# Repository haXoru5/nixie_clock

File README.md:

# Nixie Clock

## Warning, Nixie Tubes require high voltages, use caution when handling

Retro style clock built using an Arduino and IN-14 Nixie tubes

## Intro
Nixie tubes are a type of cold cathode display. They were used as numerical displays as a precursor to seven-segment displays. This project uses old Soviet IN-14 tubes to make a clock. I used KiCad 5 to design the PCB, according to JLCPCB specifications. Although this is not an in depth build guide, feel free to use this as a reference for your own nixie projects.

### Key Components
#### Nixie Tubes
IN-14 tubes were used to display digits and IN-3 tubes were used as a decimal point and blinks to indicate seconds. Nixie tubes require very high voltages, so a custom power supply was required. Resistors were used to drop the voltage and current to the appropriate levels for each tube according to their datasheets.
#### Power Supply
The nixie tubes require high voltages, so a high voltage DC-DC converter was required to step up the voltage.
#### BCD Decoder IC
Due to the high voltage, specialty BCD decoders were required to drive the nixie tubes. Additionally, they are used to isolate the high voltages from the other components. They operate by connecting the cathode to ground to turn the appropriate digit on.
#### Real Time Clock
A battery powered Real Time Clock (RTC) is used to keep the time, even if the clock is powered off.
#### Arduino
The Arduino is the controlling module and the brain to the clock. It translates the clock information sent by the RTC and instructs the ICs to display the correct time.
## Schematic
The schematic was created as follows. Custom symbols were created for several components. The library containing all components is included in this repository [here](https://github.com/haXoru5/nixie_clock/tree/main/Nixie_KiCad). Several filter capacitors were used in this design. Voltage regulators were connected to the +12V and +5V outputs to ensure a constant voltage. (This is not required for the +170V output as the nixie tubes have a generous operating voltage range). Filter capacitors were also used to reduce ripple. Ripple may cause components to misbehave, and is best practice to mitigate it as much as possible. 0.33µF capacitors were used according to the voltage regulator datasheets. Generally, one 100nF capacitor is connected in parallel with each IC to reduce high frequency noise. another 10µF capacitor was used at the +5V output to reduce low frequency noise.

## PCB
After the schematic is created, I assigned footprints to the symbols and generated a netlist.
The netlist was used to create a ratsnest which could be used to create the PCB. I put all parts apart from the nixie tubes on the back side to ease mounting and presentation in the future. Mounting holes are also drilled to mount the PCB to its housing. Apart from the nixie tubes, all parts were standard sizes and had footprints already available in the KiCad footprint libraries. The custom footprints can be found in this repository [here](https://github.com/haXoru5/nixie_clock/tree/main/Nixie_KiCad). Note that due to the high voltages, trace clearance must be increased to 0.4mm. Track width can remain the same as current is not too high. Note that depending on the PCB manufacturer, additional default settings in Pcpnew may need to be adjusted.

## Housing
WIP
## Arduino Code
The Arduino code uses the DS3231 RTC to get hours, minutes, and seconds and converts it to a BDC to display on the Nixie tubes via the K155ID1 ICs.
### Board Specific Settings
Install the megaAVR package for the Arduino Nano Every.
Ensure register emulation is off.
### Libraries
The code requires two libraries, which can be installed using their ZIP package, or by searching in the Arduino IDE
- [RTClib](https://github.com/adafruit/RTClib)
- [Adafruit BusIO](https://github.com/adafruit/Adafruit_BusIO)
## Production
### Gerbers
Generating Gerber and drill files may depend on the PCB manufacturer. As I ordered my PCB from JLCPCB, I used [their specifications](https://support.jlcpcb.com/article/149-how-to-generate-gerber-and-drill-files-in-kicad).

### Parts
The parts I used were sourced from a variety of suppliers. For a comprehensive parts list, refer to [the BOM](https://github.com/haXoru5/nixie_clock/blob/main/BOM.csv).

**Ebay**

IN-14 Nixie Tube
IN-3 Nixie Tube
High Voltage Power Supply
K155ID1 BCD Decoder IC

**Aliexpress**

DS3231 RTC
DIP Sockets
Female PCB Headers

**DigiKey**

L7812CV 12V Voltage Regulator
NJM78M05FA 5V Voltage Regulator
1/4W THT Resistors
SMT Capacitors

**Amazon**

Arduino Nano Every
### Assembly
WIP

### Future Releases
#### V2.0
- Programmable alarm function

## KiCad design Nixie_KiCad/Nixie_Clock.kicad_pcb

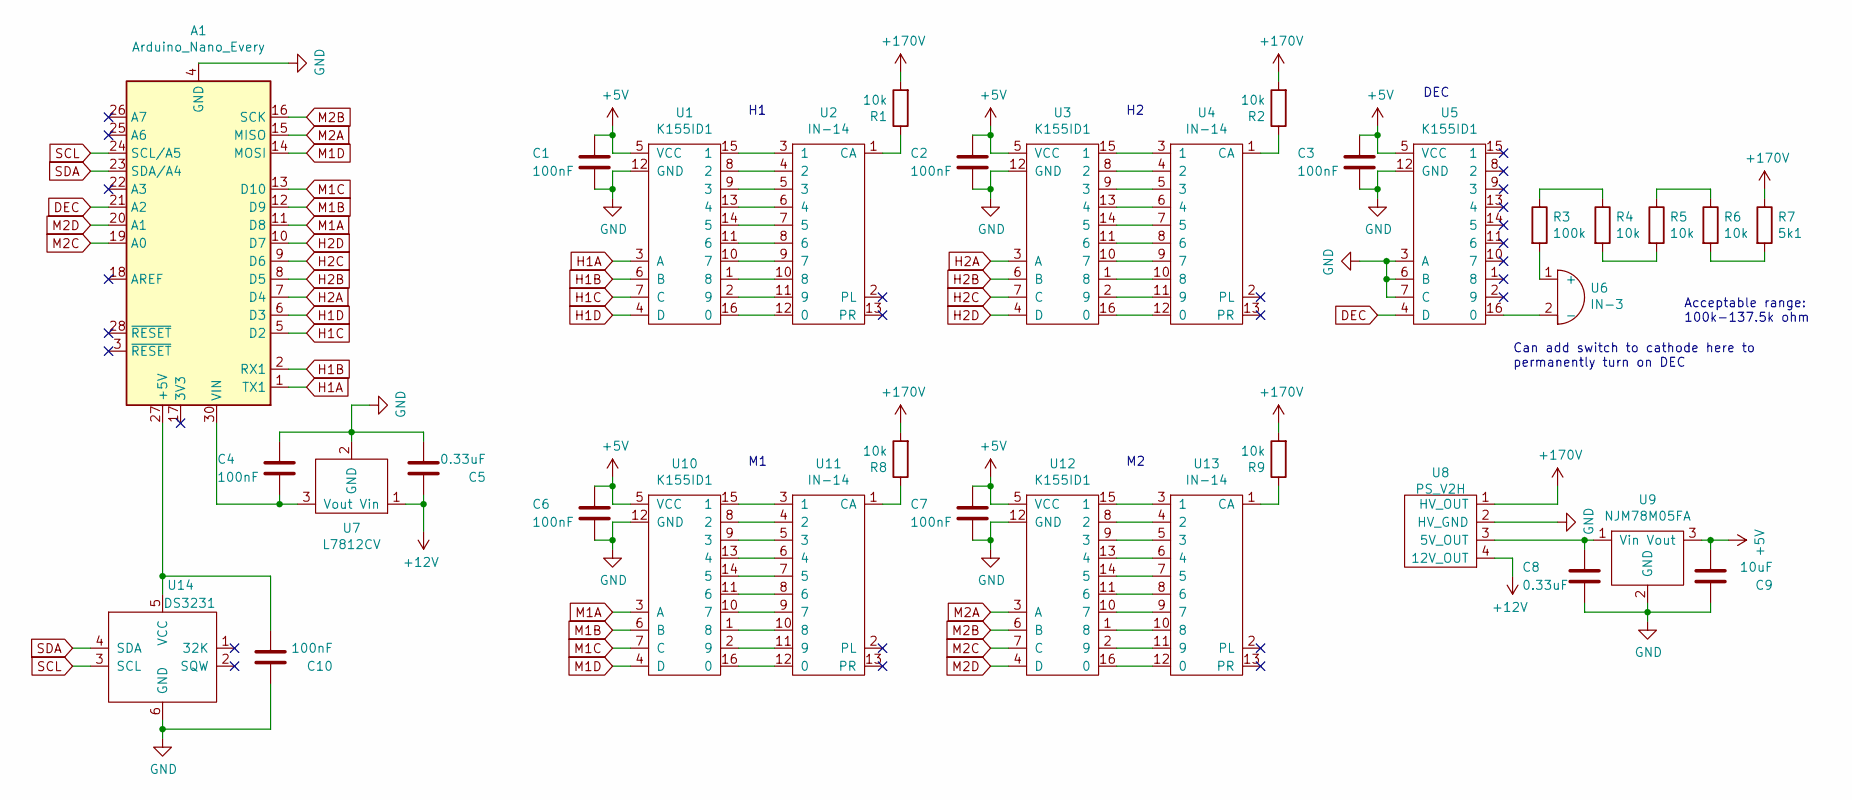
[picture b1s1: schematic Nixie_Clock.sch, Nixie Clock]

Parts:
A1: Arduino_Nano_Every; Arduino_Nano
C1, C2, C3, C4, C6, C7, C10: 100nF; C_0402_1005Metric_Pad0.74x0.62mm_HandSolder
C5, C8: 0.33uF; C_1206_3216Metric_Pad1.33x1.80mm_HandSolder
C9: 10uF; C_0805_2012Metric_Pad1.18x1.45mm_HandSolder
R1, R2, R4, R5, R6, R8, R9: 10k; R_Axial_DIN0207_L6.3mm_D2.5mm_P7.62mm_Horizontal
R3: 100k; R_Axial_DIN0207_L6.3mm_D2.5mm_P7.62mm_Horizontal
R7: 5k1; R_Axial_DIN0207_L6.3mm_D2.5mm_P7.62mm_Horizontal
U1, U3, U5, U10, U12: K155ID1
U2, U4, U11, U13: IN-14
U6: IN-3
U7: L7812CV; TO-220-3_Horizontal_TabDown
U8: PS_V2H
U9: NJM78M05FA‎; TO-220F-3_Horizontal_TabDown
U14: DS3231

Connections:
+5V: C1.2, C2.2, C3.2, C6.2, C7.2, C9.1, U1.5 (VCC), U3.5 (VCC), U5.5 (VCC), U9.3 (Vout), U10.5 (VCC), U12.5 (VCC)
+12V: C5.2, U7.1 (Vin), U8.4 (12V_OUT)
+170V: R1.2, R2.2, R7.1, R8.2, R9.2, U8.1 (HV_OUT)
DEC: A1.21 (A2), U5.4 (D)
GND: A1.4 (GND), A1.29 (GND), C1.1, C2.1, C3.1, C4.2, C5.1, C6.1, C7.1, C8.1, C9.2, C10.2, U1.12 (GND), U3.12 (GND), U5.3 (A), U5.6 (B), U5.7 (C), U5.12 (GND), U7.2 (GND), U8.2 (HV_GND), U9.2 (GND), U10.12 (GND), U12.12 (GND), U14.6 (GND)
H1A: A1.1 (TX1), U1.3 (A)
H1B: A1.2 (RX1), U1.6 (B)
H1C: A1.5 (D2), U1.7 (C)
H1D: A1.6 (D3), U1.4 (D)
H2A: A1.7 (D4), U3.3 (A)
H2B: A1.8 (D5), U3.6 (B)
H2C: A1.9 (D6), U3.7 (C)
H2D: A1.10 (D7), U3.4 (D)
M1A: A1.11 (D8), U10.3 (A)
M1B: A1.12 (D9), U10.6 (B)
M1C: A1.13 (D10), U10.7 (C)
M1D: A1.14 (MOSI), U10.4 (D)
M2A: A1.15 (MISO), U12.3 (A)
M2B: A1.16 (SCK), U12.6 (B)
M2C: A1.19 (A0), U12.7 (C)
M2D: A1.20 (A1), U12.4 (D)
unnamed: A1.27 (+5V), C10.1, U14.5 (VCC)
unnamed: A1.30 (VIN), C4.1, U7.3 (Vout)
unnamed: C8.2, U8.3 (5V_OUT), U9.1 (Vin)
unnamed: R1.1, U2.1 (CA)
unnamed: R2.1, U4.1 (CA)
unnamed: R3.1, R4.1
unnamed: R3.2, U6.1 (+)
unnamed: R4.2, R5.2
unnamed: R5.1, R6.1
unnamed: R6.2, R7.2
unnamed: R8.1, U11.1 (CA)
unnamed: R9.1, U13.1 (CA)
unnamed: U1.1 (8), U2.10 (8)
unnamed: U1.2 (9), U2.11 (9)
unnamed: U1.8 (2), U2.4 (2)
unnamed: U1.9 (3), U2.5 (3)
unnamed: U1.10 (7), U2.9 (7)
unnamed: U1.11 (6), U2.8 (6)
unnamed: U1.13 (4), U2.6 (4)
unnamed: U1.14 (5), U2.7 (5)
unnamed: U1.15 (1), U2.3 (1)
unnamed: U1.16 (0), U2.12 (0)
unnamed: U3.1 (8), U4.10 (8)
unnamed: U3.2 (9), U4.11 (9)
unnamed: U3.8 (2), U4.4 (2)
unnamed: U3.9 (3), U4.5 (3)
unnamed: U3.10 (7), U4.9 (7)
unnamed: U3.11 (6), U4.8 (6)
unnamed: U3.13 (4), U4.6 (4)
unnamed: U3.14 (5), U4.7 (5)
unnamed: U3.15 (1), U4.3 (1)
unnamed: U3.16 (0), U4.12 (0)
unnamed: U5.16 (0), U6.2 (-)
unnamed: U10.1 (8), U11.10 (8)
unnamed: U10.2 (9), U11.11 (9)
unnamed: U10.8 (2), U11.4 (2)
unnamed: U10.9 (3), U11.5 (3)
unnamed: U10.10 (7), U11.9 (7)
unnamed: U10.11 (6), U11.8 (6)
unnamed: U10.13 (4), U11.6 (4)
unnamed: U10.14 (5), U11.7 (5)
unnamed: U10.15 (1), U11.3 (1)
unnamed: U10.16 (0), U11.12 (0)
unnamed: U12.1 (8), U13.10 (8)
unnamed: U12.2 (9), U13.11 (9)
unnamed: U12.8 (2), U13.4 (2)
unnamed: U12.9 (3), U13.5 (3)
unnamed: U12.10 (7), U13.9 (7)
unnamed: U12.11 (6), U13.8 (6)
unnamed: U12.13 (4), U13.6 (4)
unnamed: U12.14 (5), U13.7 (5)
unnamed: U12.15 (1), U13.3 (1)
unnamed: U12.16 (0), U13.12 (0)
SCL: A1.24 (SCL/A5), U14.3 (SCL)
SDA: A1.23 (SDA/A4), U14.4 (SDA)

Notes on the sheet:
DEC
Acceptable range: 100k-137.5k ohm
Can add switch to cathode here to permanently turn on DEC

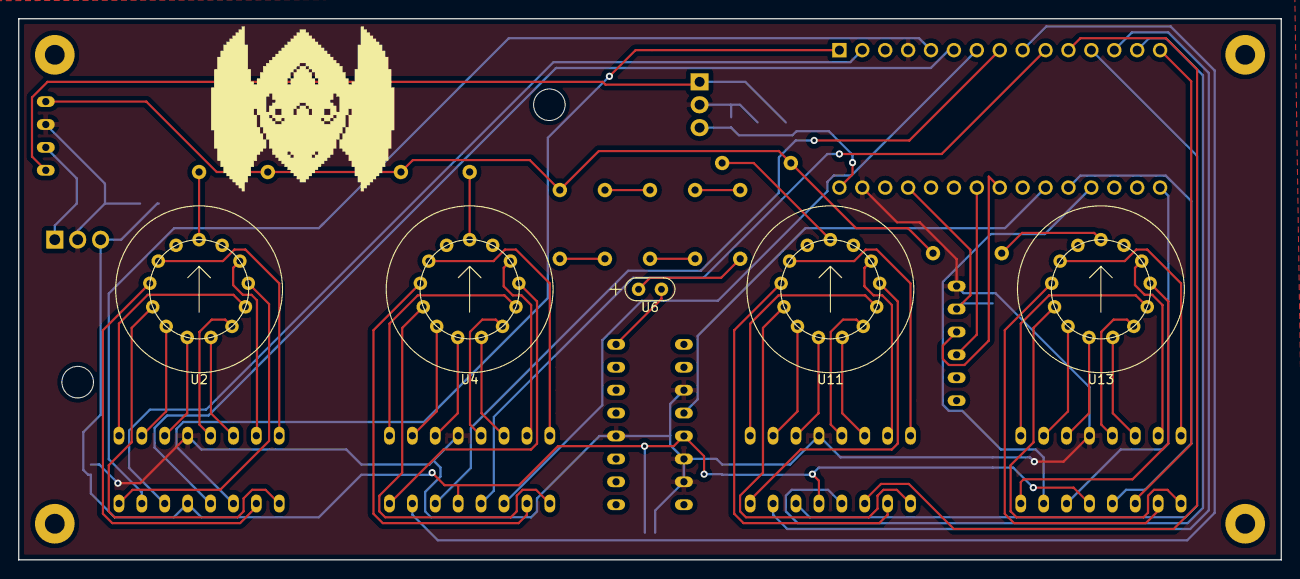
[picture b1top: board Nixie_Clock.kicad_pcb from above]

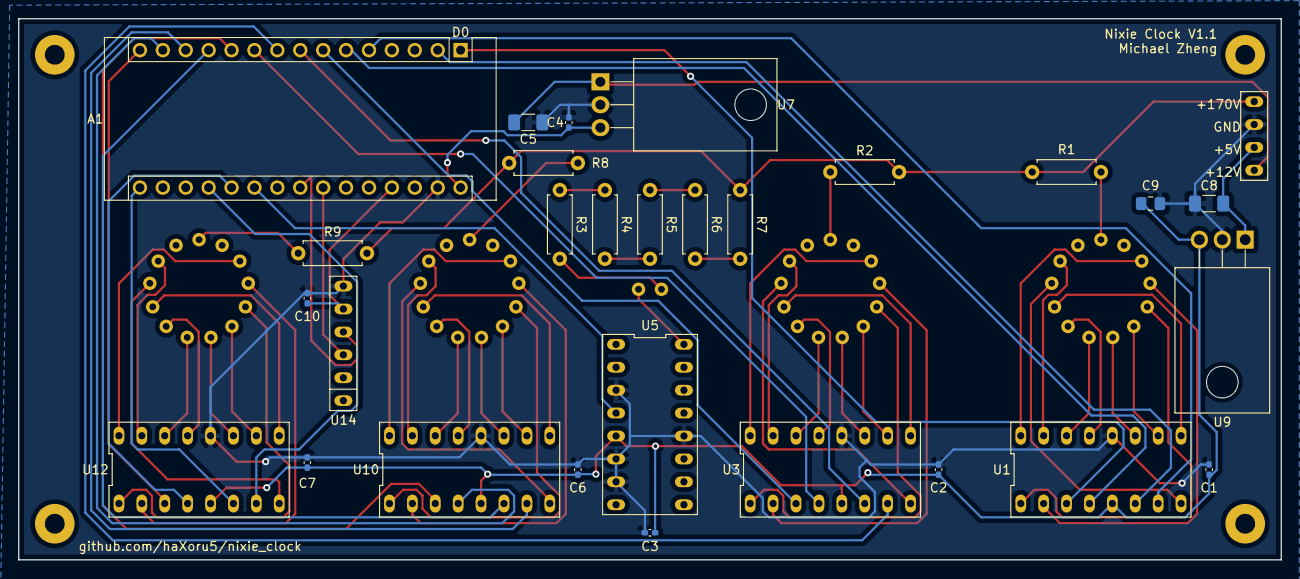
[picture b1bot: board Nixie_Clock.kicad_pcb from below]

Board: 2 copper layers, 140.0 x 60.0 mm, 34 parts (29 on the bottom side), 76 nets.

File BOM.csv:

Reference, Quantity, Value, Footprint, Datasheet
A1 ,1,Arduino_Nano_Every,Module:Arduino_Nano,https://content.arduino.cc/assets/NANOEveryV3.0_sch.pdf
C1 C2 C3 C4 C6 C7 C10 ,7,100nF,Capacitor_SMD:C_0402_1005Metric_Pad0.74x0.62mm_HandSolder,~
C5 C8 ,2,0.33uF,Capacitor_SMD:C_1206_3216Metric_Pad1.33x1.80mm_HandSolder,~
C9 ,1,10uF,Capacitor_SMD:C_0805_2012Metric_Pad1.18x1.45mm_HandSolder,~
R1 R2 R4 R5 R6 R8 R9 ,7,10k,Resistor_THT:R_Axial_DIN0207_L6.3mm_D2.5mm_P7.62mm_Horizontal,~
R3 ,1,100k,Resistor_THT:R_Axial_DIN0207_L6.3mm_D2.5mm_P7.62mm_Horizontal,~
R7 ,1,5k1,Resistor_THT:R_Axial_DIN0207_L6.3mm_D2.5mm_P7.62mm_Horizontal,~
U1 U3 U5 U10 U12 ,5,K155ID1,Nixie_Clock_Footprint:K155ID1,https://tubehobby.com/datasheets/k155id1.pdf
U2 U4 U11 U13 ,4,IN-14,Nixie_Clock_Footprint:IN-14,https://tubehobby.com/datasheets/in14.pdf
U14 ,1,DS3231,Nixie_Clock_Footprint:DS3231,https://datasheets.maximintegrated.com/en/ds/DS3231.pdf
U6 ,1,IN-3,Nixie_Clock_Footprint:IN-3,http://www.tube-tester.com/sites/nixie/dat_arch/IN-3.pdf
U7 ,1,L7812CV,Nixie_Clock_Footprint:SIP-3,https://www.st.com/content/ccc/resource/technical/document/d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
U8 ,1,PS_V2H,Nixie_Clock_Footprint:PS_V2H,https://github.com/haXoru5/nixie_clock/blob/main/Docs/PS_V2H.pdf
U9 ,1,NJM78M05FA?,Nixie_Clock_Footprint:SIP-3,https://www.nisshinbo-microdevices.co.jp/en/pdf/datasheet/NJ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

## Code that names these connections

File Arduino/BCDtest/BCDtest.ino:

#include "RTClib.h"

RTC_DS3231 rtc;

#define H1A 1
#define H1B 0
#define H1C 2
#define H1D 3
#define H2A 4
#define H2B 5
#define H2C 6
#define H2D 7
#define M1A 8
#define M1B 9
#define M1C 10
#define M1D 11
#define M2A 12
#define M2B 13
#define M2C A0
#define M2D A1
#define DECIMAL A2

char Apins[4] = {H1A, H2A, M1A, M2A};   //matrix to determine BCD output
char Bpins[4] = {H1B, H2B, M1B, M2B};
char Cpins[4] = {H1C, H2C, M1C, M2C};
char Dpins[4] = {H1D, H2D, M1D, M2D};
char Epins[1] = {DECIMAL};  //allows for future alarm to use same IC

#define H1 0
#define H2 1
#define M1 2
#define M2 3

void setup()
{
  Serial.begin(57600);

#ifndef ESP8266
  while (!Serial)
    ; // wait for serial port to connect. Needed for native USB
#endif

  if (!rtc.begin())
  {
    Serial.println("Couldn't find RTC");
    Serial.flush();
    while (1)
      delay(10);
  }
  if (rtc.lostPower())
  {
    Serial.println("RTC lost power, let's set the time!");
    rtc.adjust(DateTime(F(__DATE__), F(__TIME__)));   //sets RTC time if lost power
  }
    //rtc.adjust(DateTime(F(__DATE__), F(__TIME__)));   //uncomment to set time

  pinMode(H1A, OUTPUT);
  pinMode(H1B, OUTPUT);
  pinMode(H1C, OUTPUT);
  pinMode(H1D, OUTPUT);
  pinMode(H2A, OUTPUT);
  pinMode(H2B, OUTPUT);
  pinMode(H2C, OUTPUT);
  pinMode(H2D, OUTPUT);
  pinMode(M1A, OUTPUT);
  pinMode(M1B, OUTPUT);
  pinMode(M1C, OUTPUT);
  pinMode(M1D, OUTPUT);
  pinMode(M2A, OUTPUT);
  pinMode(M2B, OUTPUT);
  pinMode(M2C, OUTPUT);
  pinMode(M2D, OUTPUT);
  pinMode(DECIMAL, OUTPUT);

}

void loop()
{
  DateTime now = rtc.now();

  Serial.print(now.year(), DEC);
  Serial.print('/');
  Serial.print(now.month(), DEC);
  Serial.print('/');
  Serial.print(now.day(), DEC);
  Serial.println();
  Serial.print(now.hour(), DEC);
  Serial.print(':');
  Serial.print(now.minute(), DEC);
  Serial.print(':');
  Serial.print(now.second(), DEC);
  Serial.println();

  BCD(H1, now.hour() / 10);
  BCD(H2, now.hour() % 10);
  BCD(M1, now.minute() / 10);
  BCD(M2, now.minute() % 10);
  if (now.second() % 2 == 0)
  {
    digitalWrite(DECIMAL, HIGH);
    Serial.println("Dec = HIGH");
  }
  else
  {
    digitalWrite(DECIMAL, LOW);
    Serial.println("Dec = LOW");
  }
  delay(1000);
}

void BCD(int digit, int value)    //switch case determines BCD value to be sent, digit determines IC number BCD should be sent to
{
  Serial.print(digit);
  Serial.print("=");
  switch (value)
  {
    case 0:
        digitalWrite(Apins[digit], LOW);
        digitalWrite(Bpins[digit], LOW);
        digitalWrite(Cpins[digit], LOW);
        digitalWrite(Dpins[digit], LOW);
      Serial.println("0000");
      break;
    case 1:
        digitalWrite(Apins[digit], HIGH);
        digitalWrite(Bpins[digit], LOW);
        digitalWrite(Cpins[digit], LOW);
        digitalWrite(Dpins[digit], LOW);
      Serial.println("0001");
      break;
    case 2:
        digitalWrite(Apins[digit], LOW);
        digitalWrite(Bpins[digit], HIGH);
        digitalWrite(Cpins[digit], LOW);
        digitalWrite(Dpins[digit], LOW);
      Serial.println("0010");
      break;
    case 3:
        digitalWrite(Apins[digit], HIGH);
        digitalWrite(Bpins[digit], HIGH);
        digitalWrite(Cpins[digit], LOW);
        digitalWrite(Dpins[digit], LOW);
      Serial.println("0011");
      break;
    case 4:
        digitalWrite(Apins[digit], LOW);
        digitalWrite(Bpins[digit], LOW);
        digitalWrite(Cpins[digit], HIGH);
        digitalWrite(Dpins[digit], LOW);
      Serial.println("0100");
      break;
    case 5:
        digitalWrite(Apins[digit], HIGH);
        digitalWrite(Bpins[digit], LOW);
        digitalWrite(Cpins[digit], HIGH);
        digitalWrite(Dpins[digit], LOW);
      Serial.println("0101");
      break;
    case 6:
        digitalWrite(Apins[digit], LOW);
        digitalWrite(Bpins[digit], HIGH);
        digitalWrite(Cpins[digit], HIGH);
        digitalWrite(Dpins[digit], LOW);
      Serial.println("0110");
      break;
    case 7:
        digitalWrite(Apins[digit], HIGH);
        digitalWrite(Bpins[digit], HIGH);
        digitalWrite(Cpins[digit], HIGH);
        digitalWrite(Dpins[digit], LOW);
      Serial.println("0111");
      break;
    case 8:
        digitalWrite(Apins[digit], LOW);
        digitalWrite(Bpins[digit], LOW);
        digitalWrite(Cpins[digit], LOW);
        digitalWrite(Dpins[digit], HIGH);
      Serial.println("1000");
      break;
    case 9:
        digitalWrite(Apins[digit], HIGH);
        digitalWrite(Bpins[digit], LOW);
        digitalWrite(Cpins[digit], LOW);
        digitalWrite(Dpins[digit], HIGH);
      Serial.println("1001");
      break;
  }
}

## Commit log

2021-12-27 Added Nixie_Lib KiCad Library
2021-12-27 Added IN-3 Tubes to Lib
2021-12-27 Added Schematic
    -Added Schematic Diagram
    -Updated Libraries
2021-12-28 removed unnecessary files
2021-12-28 Added Footprints
2021-12-29 Added PCB
    -Added PCB ratsnest
    -Added Netlist
    -Changed Arduino module
2021-12-30 Finalized Design
    - Finalized PCB design
    - Generated Gerber files
2021-12-30 Added Power Supply Datasheet
2021-12-30 Updated BOM
2021-12-30 Added Drill Holes
2021-12-30 regenerated gerbers
2022-01-03 minor updates
2022-01-06 added filter capacitors
2022-01-06 updated footprints
2022-01-07 generated gerbers
2022-01-07 Uploaded Documentation
2022-01-07 uploaded schematic image
2022-01-08 Corrected RTC pinout
2022-01-08 updated schematic to 2.0
2022-01-12 updated baud rate
2022-01-12 Added CAD files
2022-02-01 updated to internal pull up resistors
